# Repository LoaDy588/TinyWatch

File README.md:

### What is it?
Small digital wristwatch, powered by 8bit microcontroller, with 1.3inch 128x64 monochrome OLED display. Currently work in progress.

### Links
[Blog posts about development](https://loady.one/tag/tinywatch)

[Schematic, Rev2](https://files.loady.one/schematics/tiny_watch.pdf)

### BOM
|REF|Part|
|------|------|
|U1|MCP73831T-2ACI/OT|
|U2|MIC5504-2.8YM5|
|U3|MCP100-315I/TT|
|U4|PCF85063TP/1Z|
|U5|ATTINY1617-MFR|
|DISPLAY1|REX012864LWAP3N00000|
|J1|AMPHENOL 10118192-0001LF|
|Y1|ABRACON ABS07-166-32.768KHZ-T|
|SW1, SW2, SW3|C&K KXT321LHS|
|C1, C2, C9, C12, C14|4.7uF MLCC, 0603|
|C3, C5, C10, C11|1uF MLCC, 0603|
|C4, C6, C7, C8, C13|100nF MLCC, 0603|
|R1|8K2 Resistor, 0603|
|R2, R3, R4, R5, R6, R8|4K7 Resistor, 0603|
|R8, R9, R10|510K Resistor, 0603|

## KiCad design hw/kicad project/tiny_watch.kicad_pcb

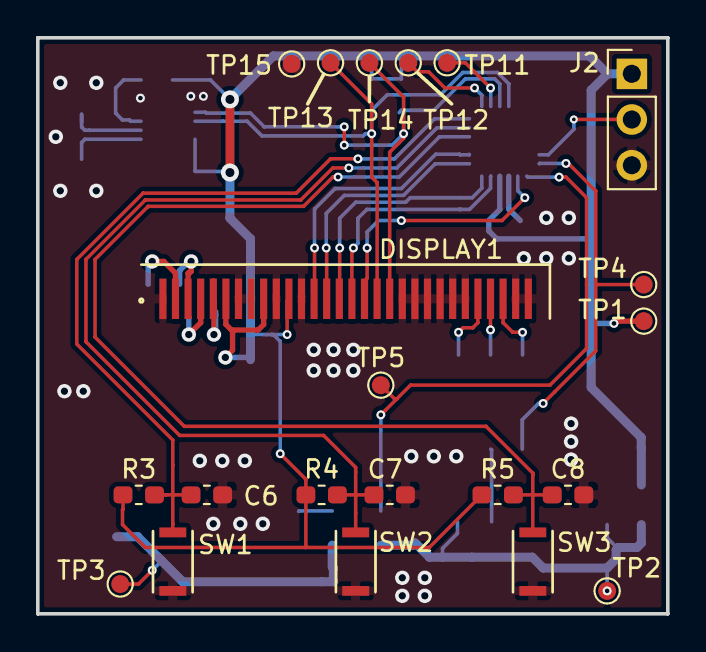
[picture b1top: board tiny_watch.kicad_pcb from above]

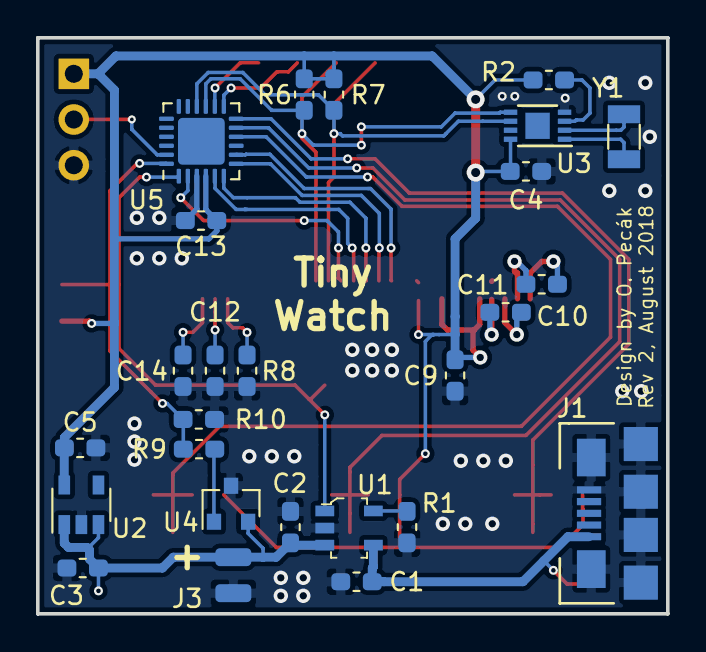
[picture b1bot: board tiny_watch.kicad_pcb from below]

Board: 2 copper layers, 35.0 x 32.0 mm, 47 parts (26 on the bottom side), 31 nets.

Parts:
C1, C2, C9, C12, C14: 4.7uF; C_0603_1608Metric_Pad1.05x0.95mm_HandSolder
C3, C5, C10, C11: 1uF; C_0603_1608Metric_Pad1.05x0.95mm_HandSolder
C4, C6, C7, C8, C13: 100nF; C_0603_1608Metric_Pad1.05x0.95mm_HandSolder
DISPLAY1: SH1106G_OLED; 30x_0.7-Pitch-display
J1: USB_B_Micro; AMPHENOL_10118192-0001LF-C
J2: PROG_HEADER; PinHeader_1x03_P2.54mm_Vertical
J3: BAT_CON; SMD_2_Wires
R1: 8K2; R_0603_1608Metric_Pad1.05x0.95mm_HandSolder
R2, R3, R4, R5, R6, R7: 4K7; R_0603_1608Metric_Pad1.05x0.95mm_HandSolder
R8, R9, R10: 510K; R_0603_1608Metric_Pad1.05x0.95mm_HandSolder
SW1, SW2, SW3: SW_Push; C_K KXT321LHS
TP1, TP2, TP3, TP4, TP5, TP11, TP12, TP13, TP14, TP15: TP; TestPoint_Pad_D1.0mm
U1: MCP73831T-2ACI_OT; SOT-753
U2: MIC5504-2.8YM5; SOT-23-5
U3: PCF85063TP; DFN-8-1EP_3x2mm_P0.5mm_EP1.36x1.46mm
U4: MCP100-315I/TT; SOT-23
U5: ATTiny1617/3217; QFN-24-1EP_4x4mm_P0.5mm_EP2.6x2.6mm
Y1: 32.768KHz; Crystal_SMD_3215-2Pin_3.2x1.5mm

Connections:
+5V: C1.2, J1.1, TP3.1, U1.4
BUTTON_1: C6.1, R3.2, SW1.2, U5.12
BUTTON_2: C7.1, R4.2, SW2.2, U5.11
BUTTON_3: C8.1, R5.2, SW3.2, U5.10
CHARGE_STAT: TP5.1, U1.1, U5.1
DISP_A0: DISPLAY1.15, U5.6
DISP_CS: DISPLAY1.13, U5.8
DISP_RDB: DISPLAY1.17, U5.2
DISP_RES: DISPLAY1.14, U5.7
DISP_WRB: DISPLAY1.16, U5.5
GND: C1.1, C2.1, C3.1, C4.1, C5.2, C6.2, C7.2, C8.2, C9.1, C12.1, C13.2, C14.1, DISPLAY1.1, DISPLAY1.7, DISPLAY1.8, DISPLAY1.10, DISPLAY1.12, DISPLAY1.20, DISPLAY1.21, DISPLAY1.22, DISPLAY1.23, DISPLAY1.24, DISPLAY1.25, DISPLAY1.29, DISPLAY1.30, J1.5, J1.6, J2.3, J3.2, R1.1, R8.1, R10.2, SW1.1, SW2.1, SW3.1, TP15.1, U1.2, U2.2, U3.4, U4.3, U5.3
LOW_BAT: R9.2, R10.1, TP4.1, U5.24
unnamed: C10.1, DISPLAY1.2
unnamed: C10.2, DISPLAY1.3
unnamed: C11.1, DISPLAY1.5
unnamed: C11.2, DISPLAY1.4
unnamed: C12.2, DISPLAY1.27
unnamed: C14.2, DISPLAY1.28
unnamed: DISPLAY1.26, R8.2
unnamed: R1.2, U1.5
unnamed: R2.1, U3.3
unnamed: R9.1, U4.1
unnamed: U3.1, Y1.1
unnamed: U3.2, Y1.2
SCL: DISPLAY1.18, R7.2, TP13.1, U3.6, U5.16
SDA: DISPLAY1.19, R6.2, TP14.1, U3.5, U5.15
UART_RX: TP12.1, U5.13
UART_TX: TP11.1, U5.14
UPDI: J2.2, U5.23
VBAT: C2.2, C3.2, J3.1, TP2.1, U1.3, U2.1, U2.3, U4.2
VDD: C4.2, C5.1, C9.2, C13.1, DISPLAY1.6, DISPLAY1.9, DISPLAY1.11, J2.1, R2.2, R3.1, R4.1, R5.1, R6.1, R7.1, TP1.1, U2.5, U3.8, U5.4

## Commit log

2018-08-23 Electronics Rev.2
2018-08-23 add RAEADME
